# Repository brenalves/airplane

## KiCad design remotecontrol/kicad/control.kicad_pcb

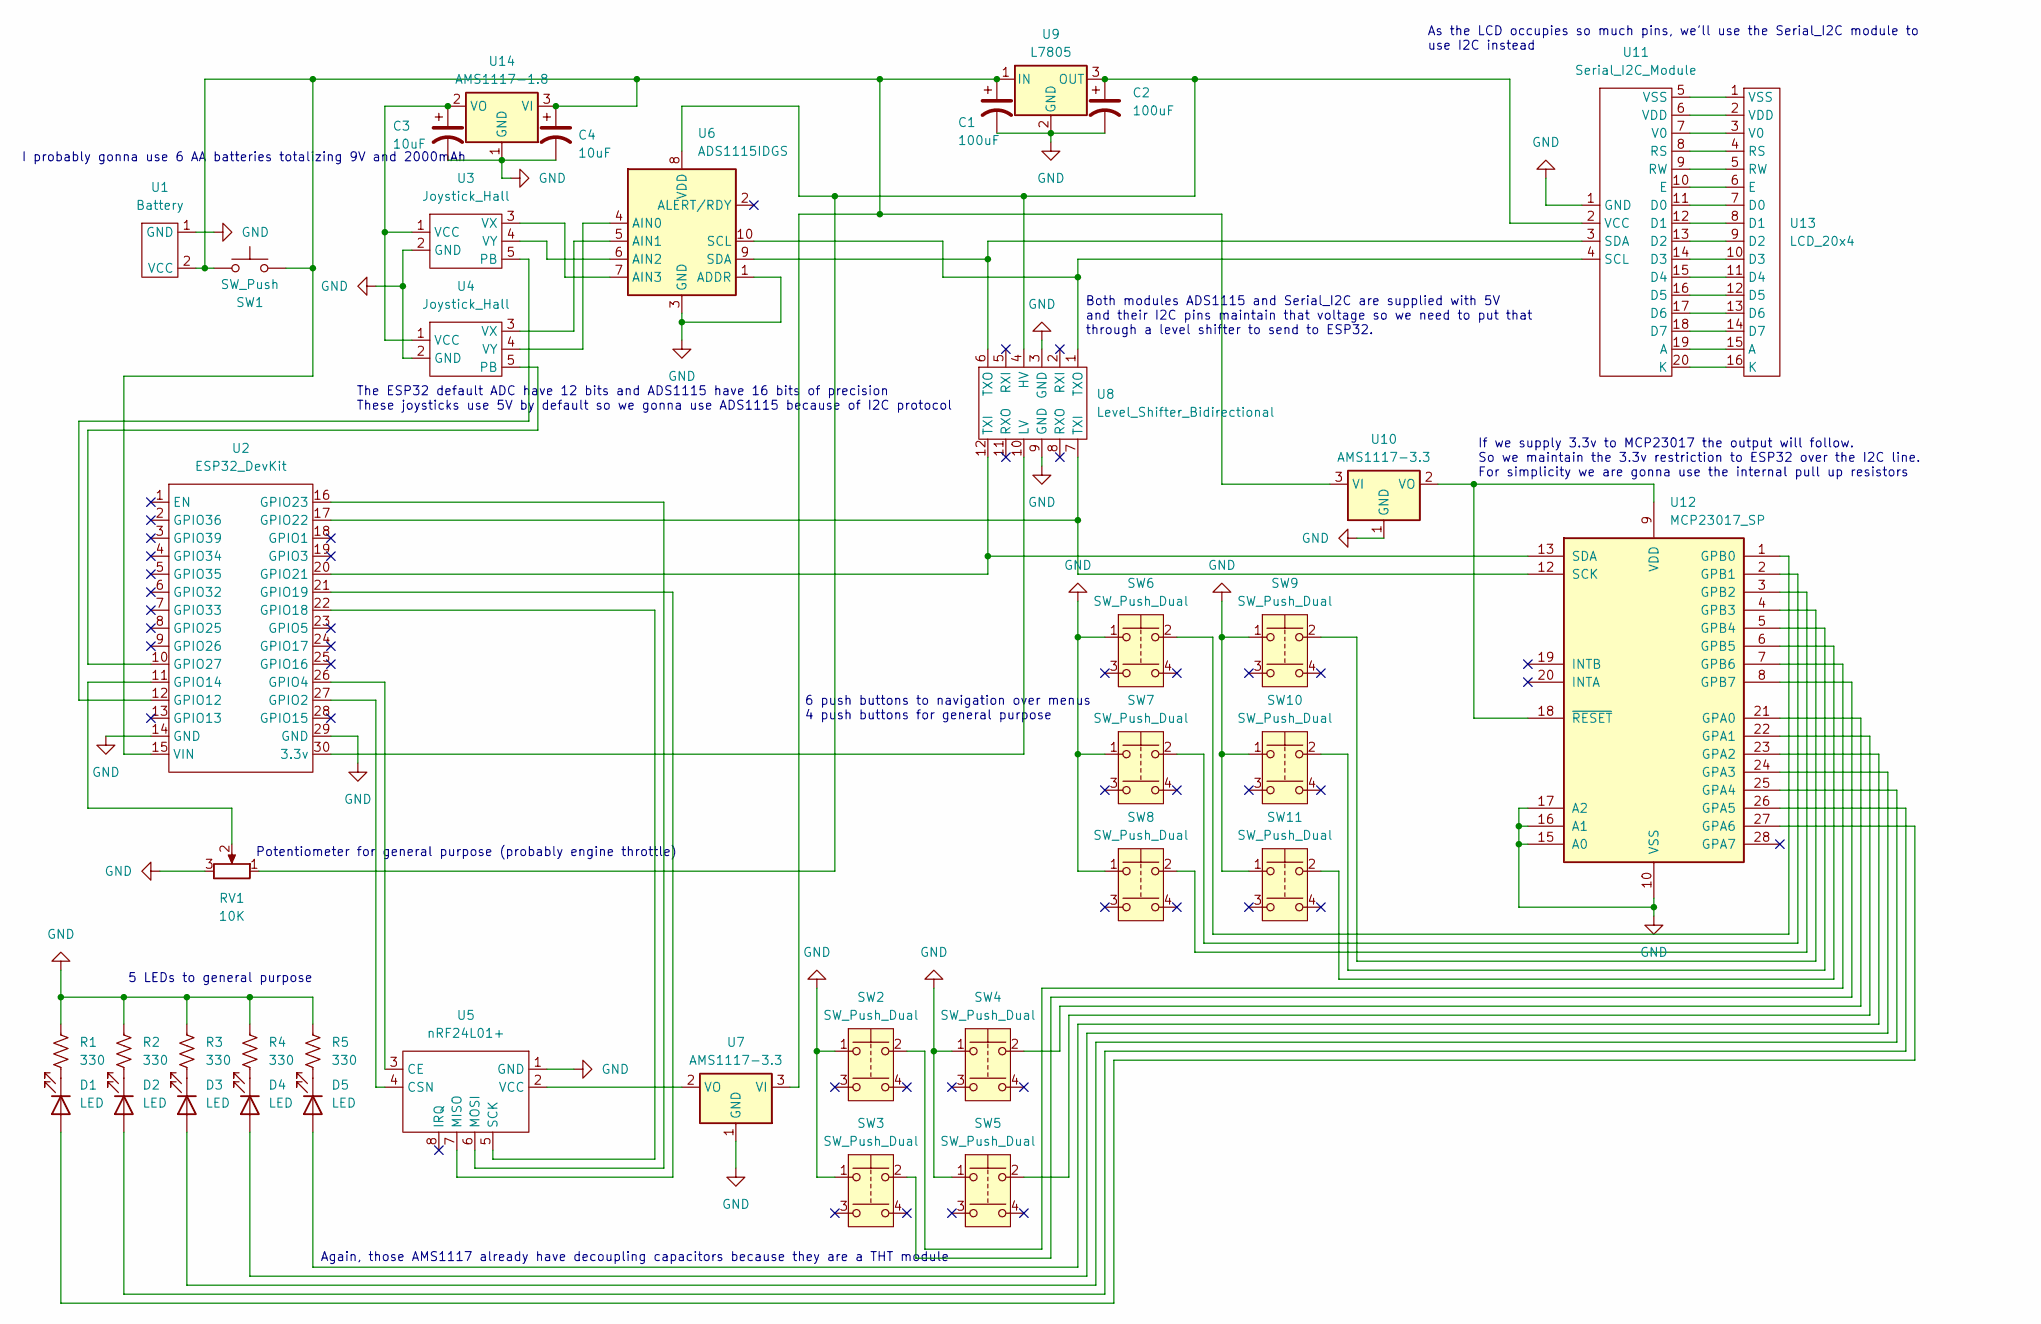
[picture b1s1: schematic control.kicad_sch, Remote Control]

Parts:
C1, C2: 100uF; CP_Radial_D5.0mm_P2.00mm
C3, C4: 10uF; CP_Radial_D5.0mm_P2.00mm
D1, D2, D3, D4, D5: LED; LED_D3.0mm
R1, R2, R3, R4, R5: 330; R_Axial_DIN0204_L3.6mm_D1.6mm_P5.08mm_Horizontal
RV1: 10K; Potentiometer_PCB_Connector_3x5.08
SW1: SW_Push; Toggle_Switch
SW2, SW3, SW4, SW5, SW6, SW7, SW8, SW9, SW10, SW11: SW_Push_Dual; SW_PUSH_6mm_H4.3mm
U1: Battery; TerminalBlock_bornier-2_P5.08mm
U2: ESP32_DevKit
U3, U4: Joystick_Hall; Joystick_Hall_Ginfull
U5: nRF24L01+
U6: ADS1115IDGS; ADS1115
U7, U10: AMS1117-3.3; PinHeader_1x03_P2.54mm_Vertical
U8: Level_Shifter_Bidirectional; Level_Shifter
U9: L7805; TO-220-3_Horizontal_TabDown
U11: Serial_I2C_Module
U12: MCP23017_SP; DIP-28_W7.62mm
U13: LCD_20x4; LCD_Display_20x4
U14: AMS1117-1.8; SOT-223-3_TabPin2

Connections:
GND: C1.2, C2.2, C3.2, C4.2, R1.1, R2.1, R3.1, R4.1, R5.1, RV1.3, SW2.1, SW3.1, SW4.1, SW5.1, SW6.1, SW7.1, SW8.1, SW9.1, SW10.1, SW11.1, U1.1 (GND), U2.14 (GND), U2.29 (GND), U3.2 (GND), U4.2 (GND), U5.1 (GND), U6.1 (ADDR), U6.3 (GND), U7.1 (GND), U8.3 (GND), U8.9 (GND), U9.2 (GND), U10.1 (GND), U11.1 (GND), U12.10 (VSS), U12.15 (A0), U12.16 (A1), U12.17 (A2), U14.1 (GND)
unnamed: D1.2 (A), U12.27 (GPA6)
unnamed: D1.1 (K), R1.2
unnamed: D2.2 (A), U12.26 (GPA5)
unnamed: D2.1 (K), R2.2
unnamed: D3.2 (A), U12.25 (GPA4)
unnamed: D3.1 (K), R3.2
unnamed: D4.2 (A), U12.24 (GPA3)
unnamed: D4.1 (K), R4.2
unnamed: D5.2 (A), U12.23 (GPA2)
unnamed: D5.1 (K), R5.2
unnamed: C1.1, C4.1, SW1.1, SW1.2, U1.2 (VCC), U2.15 (VIN), U7.3 (VI), U9.1 (IN), U10.3 (VI), U14.3 (VI)
unnamed: U2.30 (3.3v), U8.10 (LV)
unnamed: U2.27 (GPIO2), U5.4 (CSN)
unnamed: U2.26 (GPIO4), U5.3 (CE)
unnamed: U2.12 (GPIO12), U3.5 (PB)
unnamed: RV1.2, U2.11 (GPIO14)
unnamed: U2.22 (GPIO18), U5.5 (SCK)
unnamed: U2.21 (GPIO19), U5.7 (MISO)
unnamed: U2.16 (GPIO23), U5.6 (MOSI)
unnamed: U2.10 (GPIO27), U4.5 (PB)
unnamed: U3.3 (VX), U6.7 (AIN3)
unnamed: U3.4 (VY), U6.6 (AIN2)
unnamed: U4.3 (VX), U6.5 (AIN1)
unnamed: U4.4 (VY), U6.4 (AIN0)
unnamed: U5.2 (VCC), U7.2 (VO)
unnamed: U10.2 (VO), U12.9 (VDD), U12.18 (~RESET)
unnamed: U11.19 (A), U13.15 (A)
unnamed: U11.11 (D0), U13.7 (D0)
unnamed: U11.12 (D1), U13.8 (D1)
unnamed: U11.13 (D2), U13.9 (D2)
unnamed: U11.14 (D3), U13.10 (D3)
unnamed: U11.15 (D4), U13.11 (D4)
unnamed: U11.16 (D5), U13.12 (D5)
unnamed: U11.17 (D6), U13.13 (D6)
unnamed: U11.18 (D7), U13.14 (D7)
unnamed: U11.10 (E), U13.6 (E)
unnamed: U11.20 (K), U13.16 (K)
unnamed: U11.8 (RS), U13.4 (RS)
unnamed: U11.9 (RW), U13.5 (RW)
unnamed: U6.10 (SCL), U8.1 (TXO), U11.4 (SCL)
unnamed: U6.9 (SDA), U8.6 (TXO), U11.3 (SDA)
unnamed: U11.7 (V0), U13.3 (V0)
unnamed: C2.1, RV1.1, U6.8 (VDD), U8.4 (HV), U9.3 (OUT), U11.2 (VCC)
unnamed: U11.6 (VDD), U13.2 (VDD)
unnamed: U11.5 (VSS), U13.1 (VSS)
unnamed: SW4.2, U12.21 (GPA0)
unnamed: SW5.2, U12.22 (GPA1)
unnamed: SW6.2, U12.1 (GPB0)
unnamed: SW7.2, U12.2 (GPB1)
unnamed: SW8.2, U12.3 (GPB2)
unnamed: SW9.2, U12.4 (GPB3)
unnamed: SW10.2, U12.5 (GPB4)
unnamed: SW11.2, U12.6 (GPB5)
unnamed: SW2.2, U12.7 (GPB6)
unnamed: SW3.2, U12.8 (GPB7)
unnamed: U2.17 (GPIO22), U8.7 (TXI), U12.12 (SCK)
unnamed: U2.20 (GPIO21), U8.12 (TXI), U12.13 (SDA)
unnamed: C3.1, U3.1 (VCC), U4.1 (VCC), U14.2 (VO)

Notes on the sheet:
I probably gonna use 6 AA batteries totalizing 9V and 2000mAh
The ESP32 default ADC have 12 bits and ADS1115 have 16 bits of precision These joysticks use 5V by default so we gonna use ADS1115 because of I2C protocol
Again, those AMS1117 already have decoupling capacitors because they are a THT module
Potentiometer for general purpose (probably engine throttle)
Both modules ADS1115 and Serial_I2C are supplied with 5V and their I2C pins maintain that voltage so we need to put that through a level shifter to send to ESP32.
As the LCD occupies so much pins, we'll use the Serial_I2C module to use I2C instead
5 LEDs to general purpose
6 push buttons to navigation over menus 4 push buttons for general purpose
If we supply 3.3v to MCP23017 the output will follow. So we maintain the 3.3v restriction to ESP32 over the I2C line. For simplicity we are gonna use the internal pull up resistors

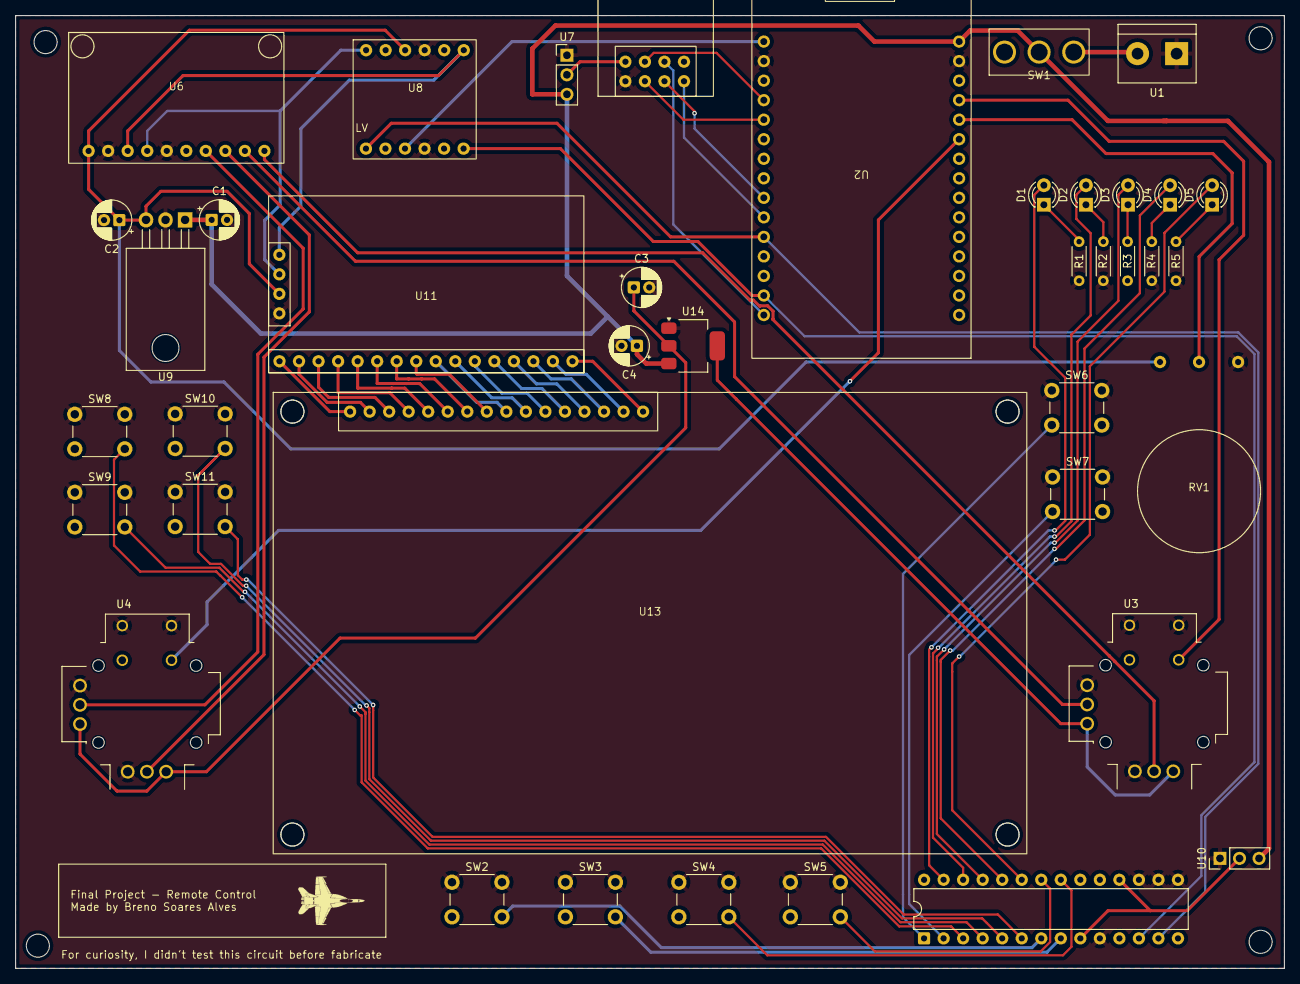
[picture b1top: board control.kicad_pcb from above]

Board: 2 copper layers, 165.0 x 123.9 mm, 40 parts (0 on the bottom side), 59 nets.

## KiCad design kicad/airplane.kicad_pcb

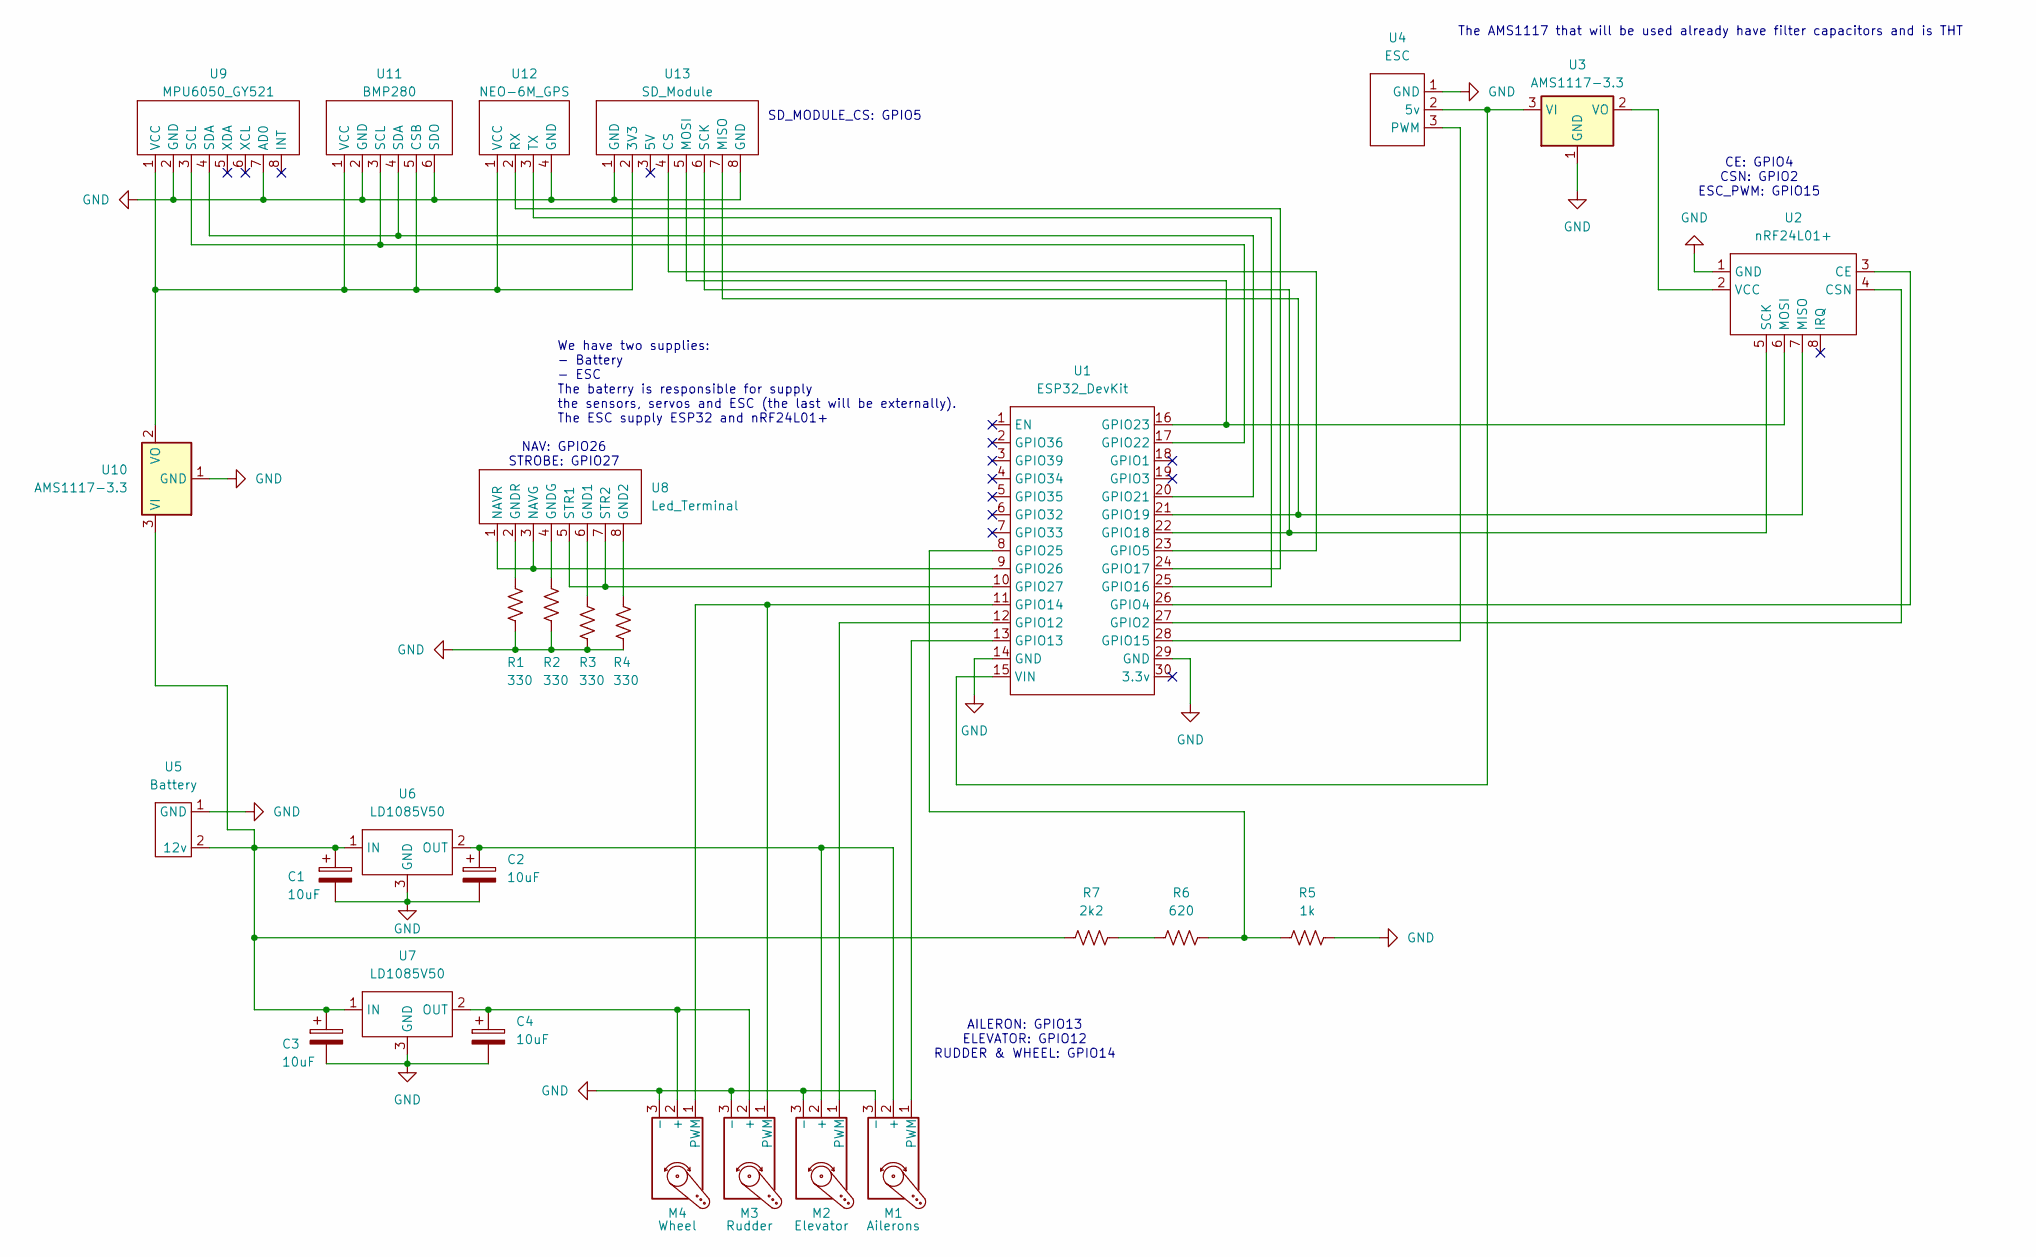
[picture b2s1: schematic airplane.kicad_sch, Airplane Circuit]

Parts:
C1, C2, C3, C4: 10uF; CP_Radial_D4.0mm_P1.50mm
M1: Ailerons; PinHeader_1x03_P2.54mm_Vertical
M2: Elevator; PinHeader_1x03_P2.54mm_Vertical
M3: Rudder; PinHeader_1x03_P2.54mm_Vertical
M4: Wheel; PinHeader_1x03_P2.54mm_Vertical
R1, R2, R3, R4: 330; R_Axial_DIN0204_L3.6mm_D1.6mm_P5.08mm_Horizontal
R5: 1k; R_Axial_DIN0204_L3.6mm_D1.6mm_P5.08mm_Horizontal
R6: 620; R_Axial_DIN0204_L3.6mm_D1.6mm_P5.08mm_Horizontal
R7: 2k2; R_Axial_DIN0204_L3.6mm_D1.6mm_P5.08mm_Horizontal
U1: ESP32_DevKit
U2: nRF24L01+
U3, U10: AMS1117-3.3; PinHeader_1x03_P2.54mm_Vertical
U4: ESC; PinHeader_1x03_P2.54mm_Vertical
U5: Battery; TerminalBlock_bornier-2_P5.08mm
U6, U7: LD1085V50; TO-220-3_Vertical
U8: Led_Terminal; TerminalBlock_bornier-8_P5.08mm
U9: MPU6050_GY521
U11: BMP280
U12: NEO-6M_GPS; NEO_6M_GPS
U13: SD_Module; SD_Card_Module

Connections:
GND: C1.2, C2.2, C3.2, C4.2, M1.3 (-), M2.3 (-), M3.3 (-), M4.3 (-), R1.2, R2.2, R3.2, R4.2, R5.2, U1.14 (GND), U1.29 (GND), U2.1 (GND), U3.1 (GND), U4.1 (GND), U5.1 (GND), U6.3 (GND), U7.3 (GND), U9.2 (GND), U9.7 (AD0), U10.1 (GND), U11.2 (GND), U11.6 (SDO), U12.4 (GND), U13.1 (GND), U13.8 (GND)
unnamed: C2.1, M1.2 (+), M2.2 (+), U6.2 (OUT)
unnamed: M1.1 (PWM), U1.13 (GPIO13)
unnamed: M2.1 (PWM), U1.12 (GPIO12)
unnamed: C4.1, M3.2 (+), M4.2 (+), U7.2 (OUT)
unnamed: M3.1 (PWM), M4.1 (PWM), U1.11 (GPIO14)
unnamed: R6.1, R7.2
unnamed: U1.27 (GPIO2), U2.4 (CSN)
unnamed: U1.26 (GPIO4), U2.3 (CE)
unnamed: U1.23 (GPIO5), U13.4 (CS)
unnamed: U1.28 (GPIO15), U4.3 (PWM)
unnamed: U1.25 (GPIO16), U12.3 (TX)
unnamed: U1.24 (GPIO17), U12.2 (RX)
unnamed: U1.22 (GPIO18), U2.5 (SCK), U13.6 (SCK)
unnamed: U1.21 (GPIO19), U2.7 (MISO), U13.7 (MISO)
unnamed: U1.20 (GPIO21), U9.4 (SDA), U11.4 (SDA)
unnamed: U1.17 (GPIO22), U9.3 (SCL), U11.3 (SCL)
unnamed: U1.16 (GPIO23), U2.6 (MOSI), U13.5 (MOSI)
unnamed: R5.1, R6.2, U1.8 (GPIO25)
unnamed: U1.9 (GPIO26), U8.1 (NAVR), U8.3 (NAVG)
unnamed: U1.10 (GPIO27), U8.5 (STR1), U8.7 (STR2)
unnamed: U1.15 (VIN), U3.3 (VI), U4.2 (5v)
unnamed: U2.2 (VCC), U3.2 (VO)
unnamed: R3.1, U8.6 (GND1)
unnamed: R4.1, U8.8 (GND2)
unnamed: R2.1, U8.4 (GNDG)
unnamed: R1.1, U8.2 (GNDR)
unnamed: C1.1, C3.1, R7.1, U5.2 (12v), U6.1 (IN), U7.1 (IN), U10.3 (VI)
unnamed: U9.1 (VCC), U10.2 (VO), U11.1 (VCC), U11.5 (CSB), U12.1 (VCC), U13.2 (3V3)

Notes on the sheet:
AILERON: GPIO13 ELEVATOR: GPIO12 RUDDER & WHEEL: GPIO14
SD_MODULE_CS: GPIO5
NAV: GPIO26 STROBE: GPIO27
We have two supplies: - Battery - ESC The baterry is responsible for supply the sensors, servos and ESC (the last will be externally). The ESC supply ESP32 and nRF24L01+
CE: GPIO4 CSN: GPIO2 ESC_PWM: GPIO15
The AMS1117 that will be used already have filter capacitors and is THT

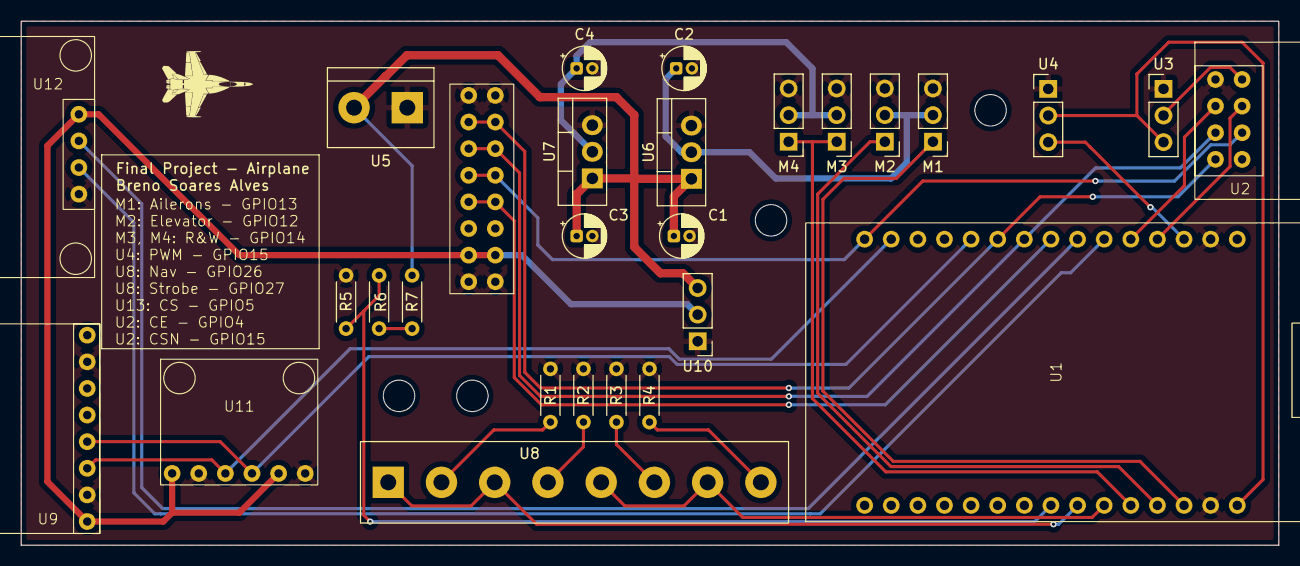
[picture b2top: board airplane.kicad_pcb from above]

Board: 2 copper layers, 120.0 x 50.0 mm, 28 parts (0 on the bottom side), 29 nets.

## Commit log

2025-08-16 Aysha linda do meu coração, ajudou no tcc
2025-08-20 control circuito started, control code started too
2025-08-20 i forgot to save kicad haha
2025-08-21 control circuit finished, control menu code finished
2025-09-05 airplane full pcb done
2025-09-07 remote control schematic done, waiting revision
2025-09-08 remote control partial pcb done, need to verify joystick and pot dimensions, also need professor check
2025-09-08 remote control done need inspection
2025-09-09 fabrication files created, waiting revision yet
